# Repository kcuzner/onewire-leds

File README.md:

# One-wire LED

## Purpose

This project is part of a larger team design project. This particular portion
is an RGB LED controlled by its own power wire using a variant of the 1-wire
protocol.

## Protocol

The standard 1-wire protocol uses only two lines: power and ground. Data is
transmitted to and from slave devices by a master device by toggling the power
line low for short periods of time. The slave devices maintain their power
during these short losses using a diode-capacitor rectifier circuit. However,
this protocol is not suitable for devices requiring more than a few hundred
microamps due to the fact that a large pullup resistor is used on the power
line and drawing too much current causes an unacceptable voltage drop.

This device uses a modified version of the protocol that sacrifices the
bi-directionality of the protocol for the ability to supply comparatively large
amounts of current to attached devices. This is accomplished by using a
P-channel MOSFET to switch the power off on the master side in short intervals.
No pull-up resistor is used and there is no corresponding open collector
transistor on the slave devices (thus removing the bi-directional capability).
So long as the capacitor on the slave side of the bus is large enough to
sustain their individual current draw, the bus can provide both data and power
to devices requiring several several 10s of milliamps of current to operate
property (such as an RGB led controller).

This protcol has been modified from the actual 1-wire specification to be
simpler to use with a 100KHz tick rate on the master in addition to necessary
modifications due to the loss of bidirectionality.

The protocol is as follows:
 * A reset is performed by holding the line low for 480uS. This device will
   listen for a continuously low input for the full 480uS without any additional
   edges. The master should allow the line to float for another 480uS. Normally,
   the presence pulse would be read during this time. However, there is no
   presence pulse in this system.
 * Following a reset, A falling edge must occur within 70uS. This marks the
   start of the LSB of the transmitted byte.
 * To write a 0, the master brings the line low for 60uS. The slave will sample
   between 20-30uS following the falling edge. Following this, the master will
   allow the line to float for 10uS before beginning the next bit.
 * To write a 1, the master brings the line low for 10uS and releases it. The
   slave will sample between 20-30uS following the falling edge. The master will
   allow the line to float for 60uS after the initial low pulse.
 * A transaction consists of the reset pulse following by 8 write pulses.

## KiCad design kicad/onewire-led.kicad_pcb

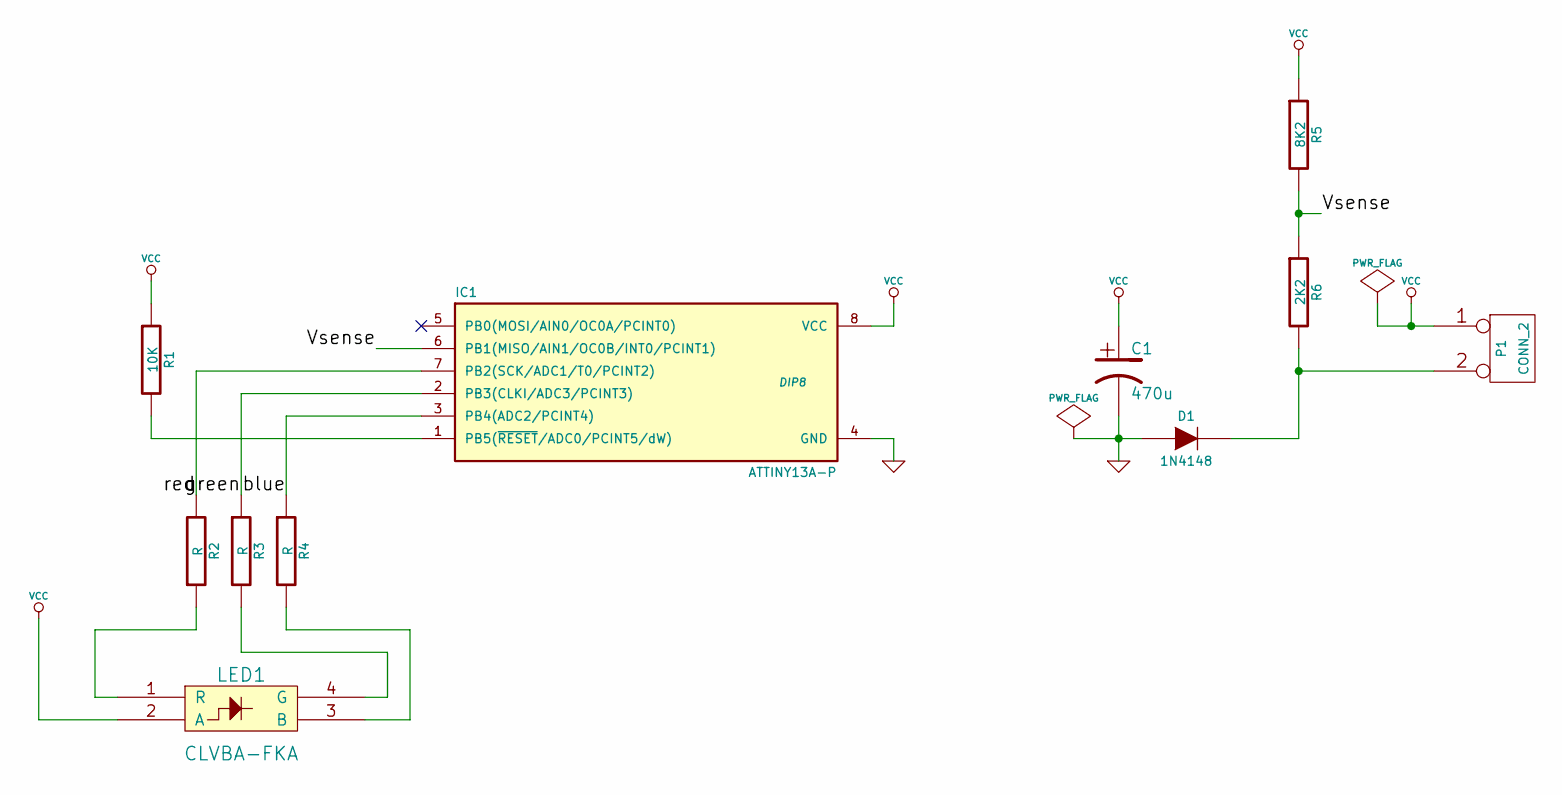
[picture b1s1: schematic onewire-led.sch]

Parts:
C1: 470u
D1: 1N4148
IC1: ATTINY13A-P; DIP8
LED1: CLVBA-FKA
P1: CONN_2
R1: 10K
R2, R3, R4: R
R5: 8K2
R6: 2K2

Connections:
/Vsense: IC1.6 (PB1(MISO/AIN1/OC0B/INT0/PCINT1)), R5.2, R6.1
/blue: IC1.3 (PB4(ADC2/PCINT4)), R4.1
/green: IC1.2 (PB3(CLKI/ADC3/PCINT3)), R3.1
/red: IC1.7 (PB2(SCK/ADC1/T0/PCINT2)), R2.2
GND: C1.2, D1.1 (A), IC1.4 (GND)
unnamed: LED1.3 (B), R4.2
unnamed: IC1.1 (PB5(~RESET~/ADC0/PCINT5/dW)), R1.2
unnamed: LED1.1 (R), R2.1
unnamed: LED1.4 (G), R3.2
unnamed: D1.2 (K), P1.2 (PM), R6.2
VCC: C1.1, IC1.8 (VCC), LED1.2 (A), P1.1, R1.1, R5.1

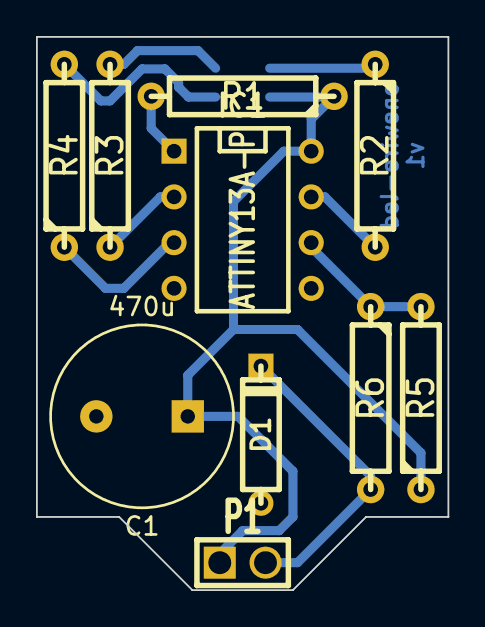
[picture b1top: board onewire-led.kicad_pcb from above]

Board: 2 copper layers, 22.9 x 30.7 mm, 11 parts (1 on the bottom side), 11 nets.

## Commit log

2015-04-04 Added install target to makefile
2015-04-04 Added LED PWM state machine and size output to Makefile
2015-04-04 Added one-wire scaffold and color selection code
2015-04-04 Added fuse programming via avr/fuses.h to Makefile
2015-04-04 Added README with description of the protocol
2015-04-05 Added initial state machine for reading the bus
2015-04-05 Added initial methods for turning off the LEDs for a time
2015-04-05 Added license
2015-04-05 Added interrupt enable instruction
2015-04-05 Fixed a missing break statement
2015-04-07 Fixed watchdog timer problems and some LED logic issues
    We are going to use the WDT, but because it's easier to work with it
    than try to work against it.
2015-04-07 Moved pins around to avoid damaging the test board
2015-04-07 Fixed one-wire configuration for a working system
    It's working...it's working!!!
2015-04-07 Fixed LED state machine for inverted values
2015-04-10 Added initial schematic without ground fills
2015-04-10 Added ground fill to bottom copper
2015-04-11 Fixed layout for package sizes and incorrect PLCC layout
2015-04-11 Reversed polarity of the onewire bus for our application
2015-04-11 Added reset toggle for debug and enabled BOD
    Turns out, BOD is important with an unreliable power supply, such as
    seen hen doing a drop-in LED replacement like this board
